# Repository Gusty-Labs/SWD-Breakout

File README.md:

# SWD Breakout

Breakout board used for connecting to a Tornado board over SWD.

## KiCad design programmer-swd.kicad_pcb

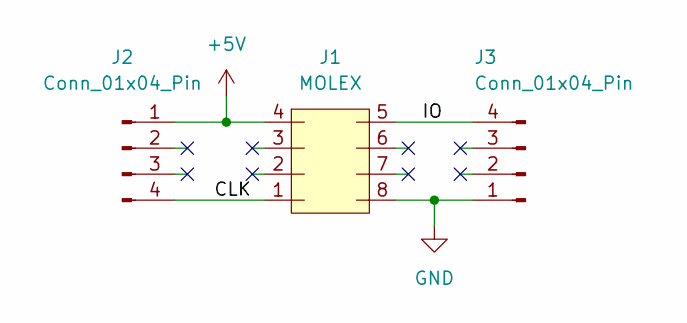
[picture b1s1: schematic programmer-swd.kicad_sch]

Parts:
J1: MOLEX; MOLEX-5050060812
J2, J3: Conn_01x04_Pin; PinHeader_1x04_P2.54mm_Vertical

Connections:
+5V: J1.4, J2.1
/CLK: J1.1, J2.4
/IO: J1.5, J3.4
GND: J1.8, J3.1

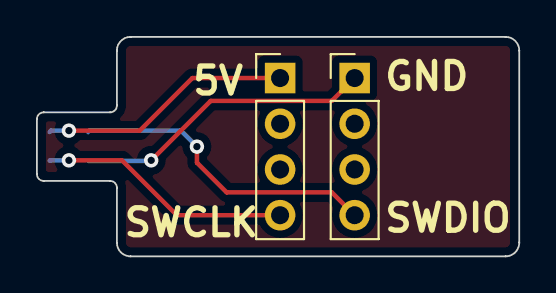
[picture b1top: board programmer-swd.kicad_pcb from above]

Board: 2 copper layers, 26.8 x 12.2 mm, 3 parts (1 on the bottom side), 4 nets.

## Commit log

2025-12-06 Added project files
2025-12-06 Fixed header connections
2025-12-06 Added 2d drawings
2025-12-06 Added Readme contents
2025-12-06 Fixed Dimensions
